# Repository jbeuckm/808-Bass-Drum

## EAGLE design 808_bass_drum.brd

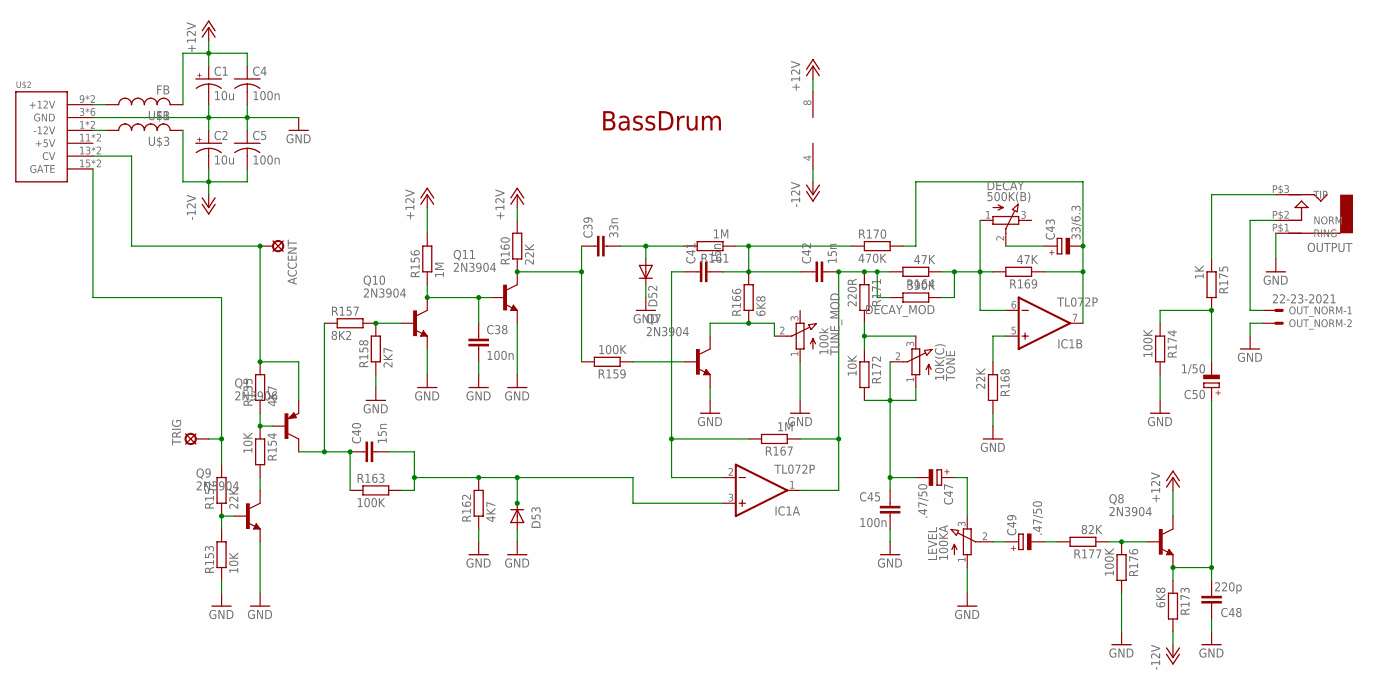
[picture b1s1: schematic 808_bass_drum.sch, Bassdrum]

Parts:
ACCENT: LSP10
C1, C2: 10u; B45181A
C4, C5, C38, C45: 100n; C050-024X044
C39: 33n; C050-024X044
C40, C41, C42: 15n; C050-024X044
C43: 33/6.3; E2,5-5
C47, C49: .47/50; E2,5-5
C48: 220p; C050-025X075
C50: 1/50; E2,5-5
D52, D53: 1N4148DO35-7; DO35-7
DECAY: 500K(B); 3RP/1610N
DECAY_MOD: 390K; 0207/7
IC1: TL072P; DIL08
LEVEL: 100KA; 3RP/1610N
OUTPUT: AUDIO-JACK; ERTHENVAR-JACK-90DEG
OUT_NORM: 22-23-2021
Q1: 2N3906; TO92
Q7, Q8, Q9, Q10, Q11: 2N3904; TO92
R152: 22K; 0207/5V
R153, R154, R172: 10K; 0207/5V
R155, R162: 4K7; 0207/5V
R156, R161, R167: 1M; 0207/7
R157: 8K2; 0207/5V
R158: 2K7; 0207/5V
R159, R174: 100K; 0207/7
R160, R168: 22K; 0207/7
R163: 100K; 0207/2V
R164, R169: 47K; 0207/7
R166: 6K8; 0309/10
R170: 470K; 0207/7
R171: 220R; 0207/7
R173: 6K8; 0207/7
R175: 1K; 0207/7
R176: 100K; 0309/10
R177: 82K; 0309/10
TONE: 10K(C); 3RP/1610N
TRIG: LSP10
TUNE_MOD: 100k; 3RP/1610N
U$1, U$3: FB
U$2: POWER; POWER_16

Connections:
+12V: C1.+, C4.1, IC1.8 (V+), Q8.1 (C), R156.2, R160.2, U$1.P$2 (2)
-12V: C2.-, C5.2, IC1.4 (V-), R173.2, U$3.P$2 (2)
C49: C49.-, R177.2
GND: C1.-, C2.+, C4.2, C5.1, C38.2, C45.2, C48.1, D52.C, D53.A, LEVEL.1 (A), OUTPUT.P$1 (RING), OUT_NORM.2, Q7.3 (E), Q9.3 (E), Q10.3 (E), Q11.3 (E), R153.1, R158.1, R162.1, R168.2, R174.2, R176.2, TUNE_MOD.1 (A), U$2.3 (GND), U$2.4 (GND), U$2.5 (GND), U$2.6 (GND), U$2.7 (GND), U$2.8 (GND)
LT_LC_OUT: OUTPUT.P$3 (TIP), R175.1
unnamed: DECAY.1 (A), DECAY_MOD.1, IC1.6 (-IN), R164.1, R169.2
unnamed: IC1.5 (+IN), R168.1
unnamed: C39.2, D52.A, R161.2
unnamed: R152.2, TRIG.MP, U$2.15 (GATE), U$2.16 (GATE)
unnamed: U$1.P$1 (1), U$2.9 (+12V), U$2.10 (+12V)
unnamed: U$2.1 (-12V), U$2.2 (-12V), U$3.P$1 (1)
unnamed: OUTPUT.P$2 (NORM), OUT_NORM.1
unnamed: C38.1, Q10.1 (C), Q11.2 (B), R156.1
unnamed: Q1.2 (B), R154.1, R155.1
unnamed: Q7.1 (C), R166.1, TUNE_MOD.2 (S)
unnamed: Q10.2 (B), R157.2, R158.2
unnamed: Q9.1 (C), R154.2
unnamed: C39.1, Q11.1 (C), R159.2, R160.1
unnamed: C40.1, Q1.1 (C), R157.1, R163.1
unnamed: C40.2, D53.C, IC1.3 (+IN), R162.2, R163.2
unnamed: Q7.2 (B), R159.1
unnamed: C41.2, C42.1, R161.1, R166.2, R170.1
unnamed: C41.1, IC1.2 (-IN), R167.2
unnamed: C42.2, DECAY_MOD.2, IC1.1 (OUT), R164.2, R167.1, R171.1
unnamed: C45.1, C47.-, R172.2, TONE.1 (A), TONE.2 (S)
unnamed: R171.2, R172.1, TONE.3 (E)
unnamed: C43.-, IC1.7 (OUT), R169.1, R170.2
unnamed: Q8.2 (B), R176.1, R177.1
unnamed: C48.2, C50.+, Q8.3 (E), R173.1
unnamed: C50.-, R174.1, R175.2
unnamed: C47.+, LEVEL.3 (E)
unnamed: C49.+, LEVEL.2 (S)
unnamed: C43.+, DECAY.2 (S)
unnamed: Q9.2 (B), R152.1, R153.2
TRIG: ACCENT.MP, Q1.3 (E), R155.2, U$2.13 (CV), U$2.14 (CV)

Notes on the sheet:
BassDrum

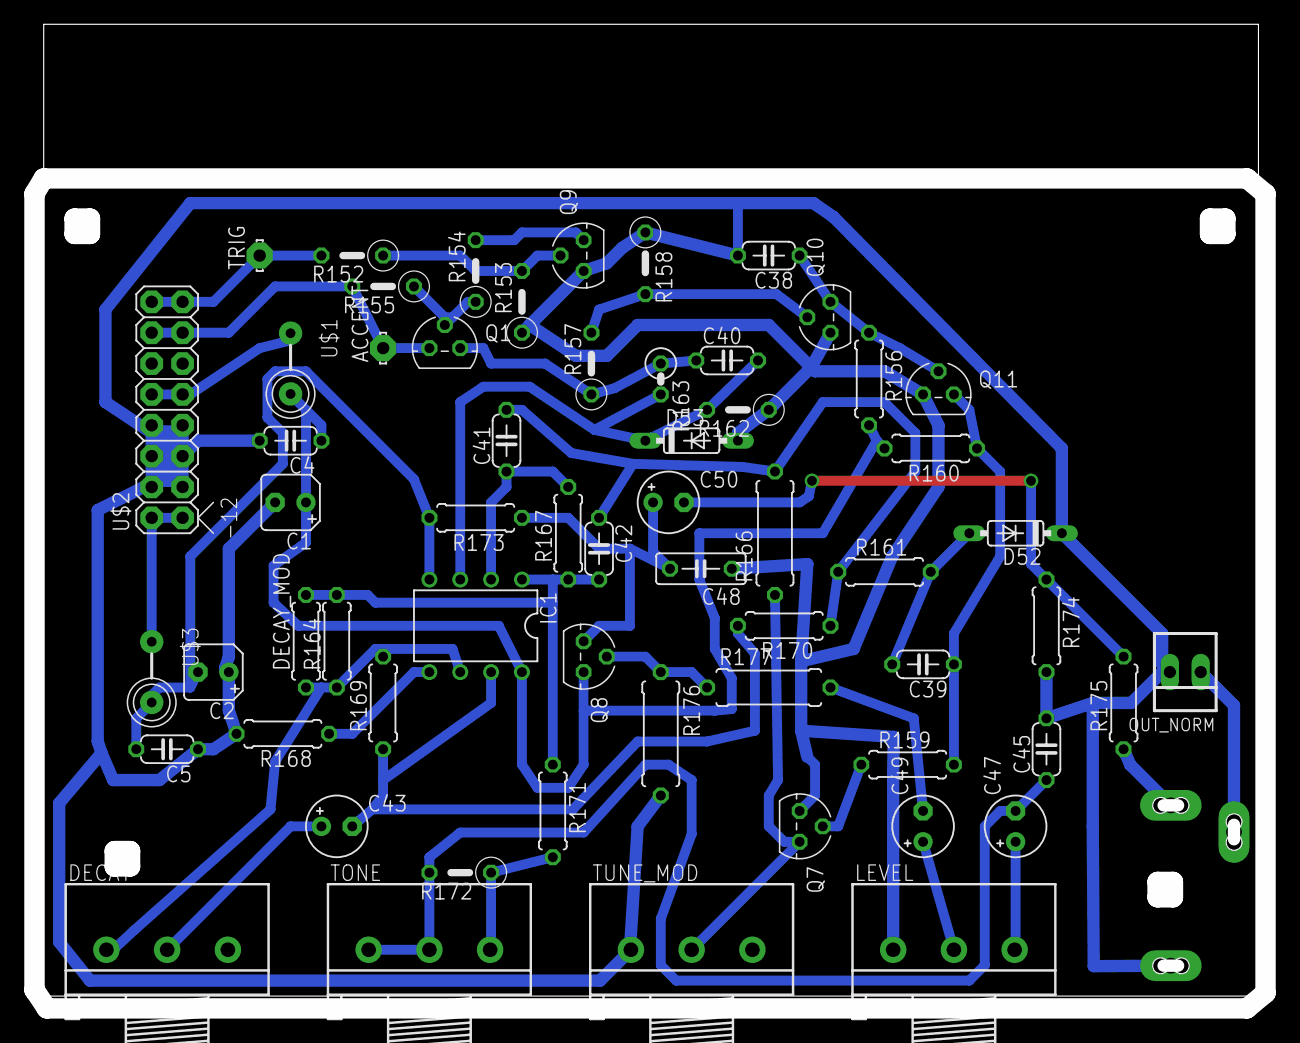
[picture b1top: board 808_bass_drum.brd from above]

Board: 2 copper layers, 101.3 x 80.2 mm, 61 parts (0 on the bottom side), 35 nets.

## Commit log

2016-05-11 updating parts and conventions
2016-05-11 placed parts again
2016-05-12 93pct ar
2016-05-12 routed
2016-05-12 cutout
2016-05-16 svg panel
2016-05-25 working with tune and decay mods
